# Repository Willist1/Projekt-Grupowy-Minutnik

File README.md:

## Projekt Grupowy Minutnika dla prelegentów

Zadania stawiane porjektowi według strony projektów grupowych:

https://projektgrupowy.eti.pg.gda.pl/editions/12/projects/3469

 5@KSME'2019 Minutnik do odmierzania czasu prezentacji 1-99 minut

edycja: 2019

klient: dr hab. inż. Marek Wójcikowski prof. nadzw. PG (opiekun PG)

opiekun: dr hab. inż. Marek Wójcikowski prof. nadzw. PG (KSME)

kierownik: -

W ramach projektu powinien powstać projekt oraz prototyp
sprzętowego minutnika do odmierzania czasu trwania prezentacji. Wymagane cechy
urządzenia:

- odmierzanie czasu: 1-99 minut z rozdzielczością 1 sekundy;

- zasilanie bateryjne oraz 5V (USB), opcjonalnie akumulator z
ładowaniem w urządzeniu;

- duży i jasny wyświetlacz (wysokość cyfry >40mm);

- łatwe ustawianie czasu prezentacji;

- sygnalizacja dźwiękowa:

    - ostrzeżenie przed końcem prezentacji (czas wyprzedzenia
ustawiany przez użytkownika);

    - zakończenia prezentacji;

    - możliwość wyłączenia sygnalizacji ostrzeżenia raz
zakończenia;

- pamięć ustawień po wyłączeniu zasilania;

- kompaktowe rozmiary;

- atrakcyjny wygląd.

 Zakres pracy:

- zapoznanie się z istniejącymi rozwiązaniami i dostępnymi
wyświetlaczami;

- do realizacji minutnika można wykorzystać gotowy moduł
mikrokontrolera;

- zapoznanie się z istniejącymi mikrokontrolerami;

- opracowanie interfejsu użytkownika;

- napisanie oprogramowania mikrokontrolera;

- wykonanie i uruchomienie prototypu urządzenia;

- zaprojektowanie i wykonanie obudowy (np. w technologii druku
3D);

- napisanie dokumentacji.

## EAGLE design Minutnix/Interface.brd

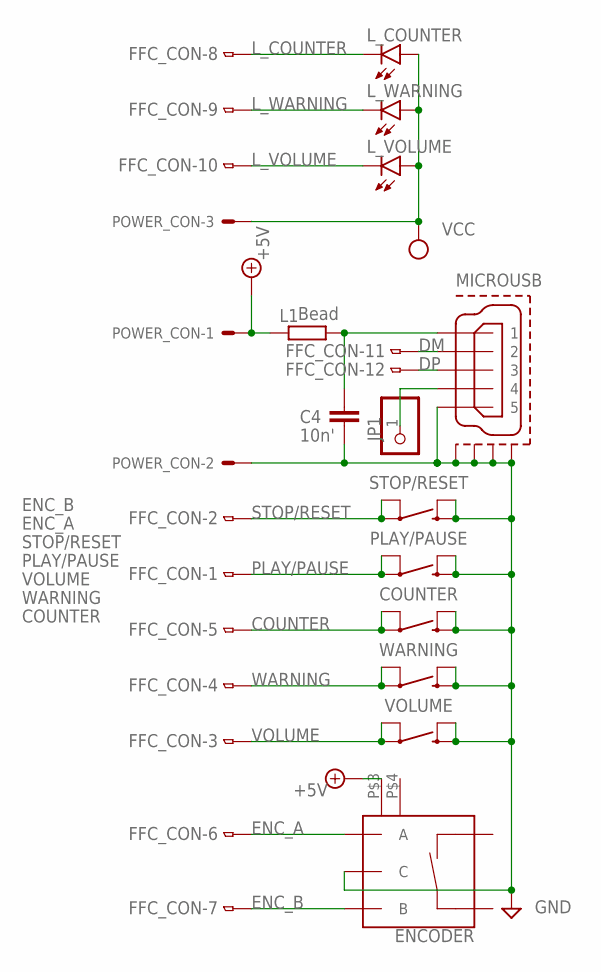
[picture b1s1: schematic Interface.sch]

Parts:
C4: 10n'; C0402
COUNTER: MOMENTARY-SWITCH-SPST-PTH-12MM; TACTILE_SWITCH_PTH_12MM
ENCODER: ENCODER-SWITCH; ROTARY_ENC_PLAIN
FFC_CON: FH12-12S-0.5S_THINNER; FH12-12S-0.5SH_THINER
JP1: PINHD-1X1; 1X01
L1: Bead; R0603
L_COUNTER: LEDCHIPLED_0805; CHIPLED_0805
L_VOLUME: LEDCHIPLED_0805; CHIPLED_0805
L_WARNING: LEDCHIPLED_0805; CHIPLED_0805
MICROUSB: MICRO-USB-RECEPTACLE; 47589-0002
PLAY/PAUSE: MOMENTARY-SWITCH-SPST-PTH-12MM; TACTILE_SWITCH_PTH_12MM
POWER_CON: JST-XH-03-PIN-LONG-PAD; JST-XH-03-PACKAGE-LONG-PAD
STOP/RESET: MOMENTARY-SWITCH-SPST-PTH-12MM; TACTILE_SWITCH_PTH_12MM
VOLUME: MOMENTARY-SWITCH-SPST-PTH-12MM; TACTILE_SWITCH_PTH_12MM
WARNING: MOMENTARY-SWITCH-SPST-PTH-12MM; TACTILE_SWITCH_PTH_12MM

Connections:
+5V: ENCODER.P$3 (GND1), L1.1, POWER_CON.1
COUNTER: COUNTER.1, COUNTER.2 (3), FFC_CON.5
DM: FFC_CON.11, MICROUSB.2
DP: FFC_CON.12, MICROUSB.3
ENC_A: ENCODER.A, FFC_CON.6
ENC_B: ENCODER.B, FFC_CON.7
GND: C4.2, COUNTER.3 (2), COUNTER.4, ENCODER.C, MICROUSB.5, MICROUSB.CASING1 (GND1), MICROUSB.CASING2 (GND2), MICROUSB.CASING3 (GND3), MICROUSB.CASING4 (GND4), PLAY/PAUSE.3 (2), PLAY/PAUSE.4, POWER_CON.2, STOP/RESET.3 (2), STOP/RESET.4, VOLUME.3 (2), VOLUME.4, WARNING.3 (2), WARNING.4
L_COUNTER: FFC_CON.8, L_COUNTER.C
L_VOLUME: FFC_CON.10, L_VOLUME.C
L_WARNING: FFC_CON.9, L_WARNING.C
unnamed: JP1.1, MICROUSB.4
unnamed: C4.1, L1.2, MICROUSB.1
PLAY/PAUSE: FFC_CON.1, PLAY/PAUSE.1, PLAY/PAUSE.2 (3)
STOP/RESET: FFC_CON.2, STOP/RESET.1, STOP/RESET.2 (3)
VCC: L_COUNTER.A, L_VOLUME.A, L_WARNING.A, POWER_CON.3
VOLUME: FFC_CON.3, VOLUME.1, VOLUME.2 (3)
WARNING: FFC_CON.4, WARNING.1, WARNING.2 (3)

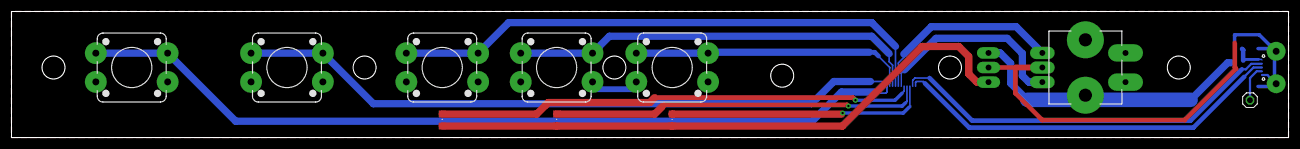
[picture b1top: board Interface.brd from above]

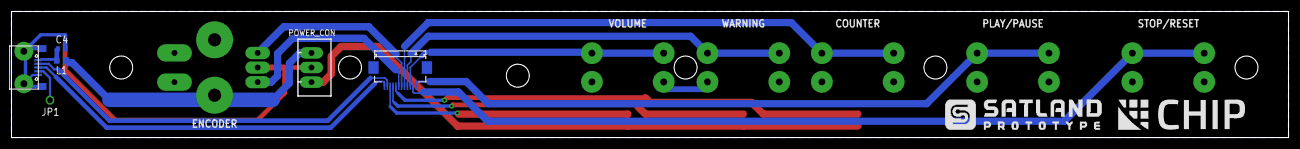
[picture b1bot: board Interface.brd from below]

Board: 2 copper layers, 222.3 x 21.9 mm, 15 parts (5 on the bottom side), 17 nets.

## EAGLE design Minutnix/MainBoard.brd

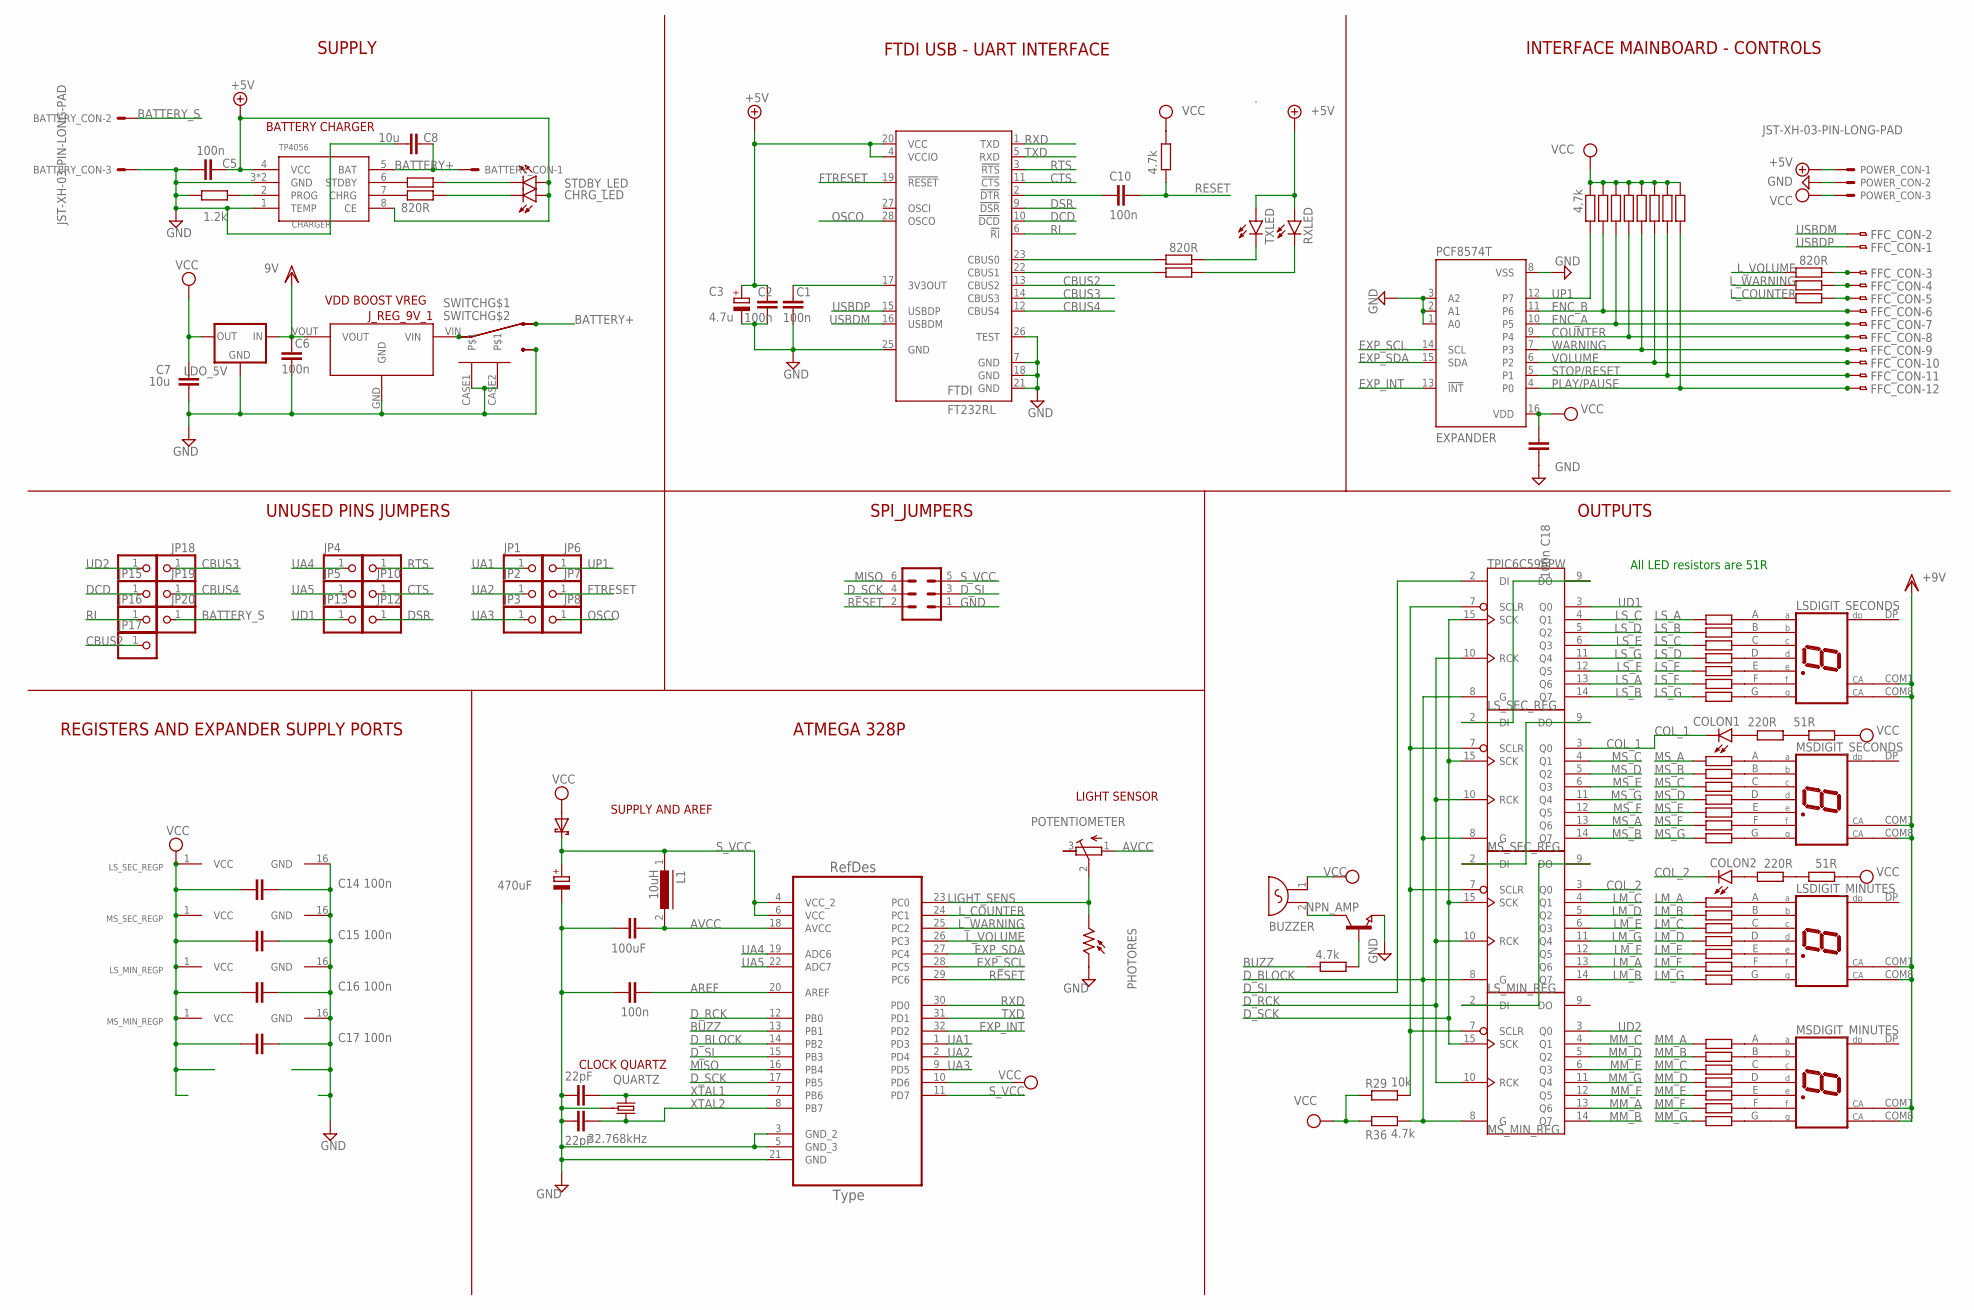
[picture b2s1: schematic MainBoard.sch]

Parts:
ATMEGA328P: ATMEGA328P-AU; QFP80P900X900X120-32N
BATTERY_CON: JST-XH-03-PIN-LONG-PAD; JST-XH-03-PACKAGE-LONG-PAD
BUZZER: F/HGP
C1, C2, C4, C5, C6, C10, C14, C15, C16, C17, C18: 100n; C0603
C3: 4.7u; SMC_B
C7, C8: 10u; C1206
C29, C30: 22pF; C0603
C31: 470uF; 153CLV-0810
C32: 100uF; C1210
CHARGER: TP4056; SOP-8
CHRG_LED: LEDCHIPLED_0603; CHIPLED_0603
COLON1, COLON2: LED5MM
EXPANDER: PCF8574T; SO16W
FFC_CON: FH12-12S-0.5S_THINNER; FH12-12S-0.5SH_THINER
FTDI: FT232RL; SSOP28
JP1, JP2, JP3, JP4, JP5, JP6, JP7, JP8, JP9, JP10, JP12, JP13, JP14, JP15, JP16, JP17, JP18, JP19, JP20: PINHD-1X1; 1X01
J_REG_9V_1: 9V_VOLTAGE_REGULATOR
L1: 10uH; DR73
LDO_5V: LM1117; SOT223
LSDIGIT_MINUTES: LED-7-SEGM-56MM; MYTHT
LSDIGIT_SECONDS: LED-7-SEGM-56MM; MYTHT
LS_MIN_REG: TPIC6C596PW; SO16
LS_SEC_REG: TPIC6C596PW; SO16
MSDIGIT_MINUTES: LED-7-SEGM-56MM; MYTHT
MSDIGIT_SECONDS: LED-7-SEGM-56MM; MYTHT
MS_MIN_REG: TPIC6C596PW; SO16
MS_SEC_REG: TPIC6C596PW; SO16
NPN_AMP: NPN-TRANSISTOR_SOT23; SOT23
PHOTORES: VT90N1; VT900
POTENTIOMETER: R-TRIMM3296Y; RTRIM3296Y
POWER_CON: JST-XH-03-PIN-LONG-PAD; JST-XH-03-PACKAGE-LONG-PAD
QUARTZ: 32.768kHz; CRYSTAL-SMD-2X6-CYL
R1, R2, R3, R4, R5, R6, R7, R8, R9, R10, R11, R12, R13, R14, R15, R16, R17, R18, R19, R20, R21, R22, R23, R24, R25, R26, R27, R28: 50; R0603
R29: 10k; R0603
R30, R31, R33, R36, R42, R43, R44, R45, R46, R56, R61: 4.7k; R0603
R32, R35: 51R; R0603
R34, R50: 220R; R0603
R39, R40, R47, R52, R64, R65, R66: 820R; R0603
R48: 1.2k; R0603
RXLED: LEDCHIPLED_0603; CHIPLED_0603
SHOTTKY: S2A; DO214AA
SPI_JUMPERS: MA03-2
STDBY_LED: LEDCHIPLED_0603; CHIPLED_0603
SWITCH: X2; MINI
TXLED: LEDCHIPLED_0603; CHIPLED_0603

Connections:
+5V: C2.2, C3.+, C5.1, CHARGER.4 (VCC), CHARGER.8 (CE), CHRG_LED.A, FTDI.4 (VCCIO), FTDI.20 (VCC), POWER_CON.1, RXLED.A, STDBY_LED.A, TXLED.A
AREF: ATMEGA328P.20 (AREF), C4.1
AVCC: ATMEGA328P.18 (AVCC), C32.1, L1.2, POTENTIOMETER.1 (A)
BATTERY+: BATTERY_CON.1, C8.2, CHARGER.5 (BAT), SWITCH.1, SWITCH.4
BATTERY_S: BATTERY_CON.2, JP20.1
BUZZ: ATMEGA328P.13 (PB1), R30.2
CBUS2: FTDI.13 (CBUS2), JP17.1
CBUS3: FTDI.14 (CBUS3), JP18.1
CBUS4: FTDI.12 (CBUS4), JP19.1
COL_1: COLON1.K (C), MS_SEC_REG.3 (Q0)
COL_2: COLON2.K (C), LS_MIN_REG.3 (Q0)
COUNTER: EXPANDER.9 (P4), FFC_CON.8, R42.2
CTS: FTDI.11 (!CTS), JP10.1
DCD: FTDI.10 (!DCD), JP15.1
DSR: FTDI.9 (!DSR), JP12.1
DTR: C10.2, FTDI.2 (!DTR)
D_BLOCK: ATMEGA328P.14 (PB2), LS_MIN_REG.8 (G), LS_SEC_REG.8 (G), MS_MIN_REG.8 (G), MS_SEC_REG.8 (G), R36.1
D_RCK: ATMEGA328P.12 (PB0), LS_MIN_REG.10 (RCK), LS_SEC_REG.10 (RCK), MS_MIN_REG.10 (RCK), MS_SEC_REG.10 (RCK)
D_SCK: ATMEGA328P.17 (PB5), LS_MIN_REG.15 (SCK), LS_SEC_REG.15 (SCK), MS_MIN_REG.15 (SCK), MS_SEC_REG.15 (SCK), SPI_JUMPERS.4
D_SI: ATMEGA328P.15 (PB3), LS_SEC_REG.2 (DI), SPI_JUMPERS.3
ENC_A: EXPANDER.10 (P5), FFC_CON.7, R33.2
ENC_B: EXPANDER.11 (P6), FFC_CON.6, R31.2
EXP_INT: ATMEGA328P.32 (PD2), EXPANDER.13 (!INT)
EXP_SCL: ATMEGA328P.28 (PC5), EXPANDER.14 (SCL)
EXP_SDA: ATMEGA328P.27 (PC4), EXPANDER.15 (SDA)
FTRESET: FTDI.19 (!RESET), JP7.1
GND: ATMEGA328P.3 (GND_2), ATMEGA328P.5 (GND_3), ATMEGA328P.21 (GND), BATTERY_CON.3, C1.1, C2.1, C3.-, C4.2, C5.2, C6.1, C7.2, C8.1, C14.1, C15.1, C16.1, C17.1, C18.1, C29.1, C30.1, C31.-, C32.2, CHARGER.1 (TEMP), CHARGER.3 (GND), CHARGER.ETP (GND), EXPANDER.1 (A0), EXPANDER.2 (A1), EXPANDER.3 (A2), EXPANDER.8 (VSS), FTDI.7 (GND), FTDI.18 (GND), FTDI.21 (GND), FTDI.25 (GND), FTDI.26 (TEST), J_REG_9V_1.GND, LDO_5V.1 (GND), LS_MIN_REG.16 (GND), LS_SEC_REG.16 (GND), MS_MIN_REG.16 (GND), MS_SEC_REG.16 (GND), NPN_AMP.2 (E), PHOTORES.1, POWER_CON.2, QUARTZ.SHEILD (GND), R48.2, SPI_JUMPERS.1, SWITCH.3, SWITCH.6, SWITCH.CASE1, SWITCH.CASE2
LIGHT_SENS: ATMEGA328P.23 (PC0), PHOTORES.2, POTENTIOMETER.2 (S)
LM_A: LS_MIN_REG.13 (Q6), R7.2
LM_B: LS_MIN_REG.14 (Q7), R6.2
LM_C: LS_MIN_REG.4 (Q1), R5.2
LM_D: LS_MIN_REG.5 (Q2), R4.2
LM_E: LS_MIN_REG.6 (Q3), R3.2
LM_F: LS_MIN_REG.12 (Q5), R2.2
LM_G: LS_MIN_REG.11 (Q4), R1.2
LS_A: LS_SEC_REG.13 (Q6), R21.2
LS_B: LS_SEC_REG.14 (Q7), R20.2
LS_C: LS_SEC_REG.4 (Q1), R19.2
LS_D: LS_SEC_REG.5 (Q2), R18.2
LS_E: LS_SEC_REG.6 (Q3), R17.2
LS_F: LS_SEC_REG.12 (Q5), R16.2
LS_G: LS_SEC_REG.11 (Q4), R15.2
L_COUNTER: ATMEGA328P.24 (PC1), R52.2
L_VOLUME: ATMEGA328P.26 (PC3), R64.2
L_WARNING: ATMEGA328P.25 (PC2), R47.2
MISO: ATMEGA328P.16 (PB4), SPI_JUMPERS.6
MM_A: MS_MIN_REG.13 (Q6), R27.2
MM_B: MS_MIN_REG.14 (Q7), R26.2
MM_C: MS_MIN_REG.4 (Q1), R25.2
MM_D: MS_MIN_REG.5 (Q2), R24.2
MM_E: MS_MIN_REG.6 (Q3), R23.2
MM_F: MS_MIN_REG.12 (Q5), R22.2
MM_G: MS_MIN_REG.11 (Q4), R28.2
MS_A: MS_SEC_REG.13 (Q6), R14.2
MS_B: MS_SEC_REG.14 (Q7), R13.2
MS_C: MS_SEC_REG.4 (Q1), R12.2
MS_D: MS_SEC_REG.5 (Q2), R11.2
MS_E: MS_SEC_REG.6 (Q3), R10.2
MS_F: MS_SEC_REG.12 (Q5), R9.2
MS_G: MS_SEC_REG.11 (Q4), R8.2
unnamed: R32.2, R50.1
unnamed: MSDIGIT_MINUTES.F, R22.1
unnamed: LSDIGIT_MINUTES.G, R1.1
unnamed: MSDIGIT_MINUTES.E, R23.1
unnamed: LSDIGIT_MINUTES.F, R2.1
unnamed: LSDIGIT_MINUTES.E, R3.1
unnamed: LSDIGIT_MINUTES.D, R4.1
unnamed: LSDIGIT_MINUTES.C, R5.1
unnamed: LSDIGIT_MINUTES.B, R6.1
unnamed: FFC_CON.3, R64.1
unnamed: MSDIGIT_MINUTES.D, R24.1
unnamed: FFC_CON.4, R47.1
unnamed: MSDIGIT_MINUTES.C, R25.1
unnamed: LS_MIN_REG.7 (SCLR), LS_SEC_REG.7 (SCLR), MS_MIN_REG.7 (SCLR), MS_SEC_REG.7 (SCLR), R29.1
unnamed: LSDIGIT_MINUTES.A, R7.1
unnamed: C1.2, FTDI.17 (3V3OUT)
unnamed: COLON2.A, R34.2
unnamed: FFC_CON.5, R52.1
unnamed: MSDIGIT_MINUTES.B, R26.1
unnamed: MSDIGIT_MINUTES.A, R27.1
unnamed: MSDIGIT_SECONDS.G, R8.1
unnamed: MSDIGIT_SECONDS.F, R9.1
unnamed: MSDIGIT_SECONDS.E, R10.1
unnamed: FTDI.23 (CBUS0), R66.2
unnamed: MSDIGIT_SECONDS.D, R11.1
unnamed: MSDIGIT_SECONDS.C, R12.1
unnamed: MSDIGIT_SECONDS.B, R13.1
unnamed: MSDIGIT_SECONDS.A, R14.1
unnamed: LSDIGIT_SECONDS.G, R15.1
unnamed: LSDIGIT_SECONDS.F, R16.1
unnamed: FTDI.22 (CBUS1), R65.2
unnamed: LSDIGIT_SECONDS.E, R17.1
unnamed: LSDIGIT_SECONDS.D, R18.1
unnamed: LSDIGIT_SECONDS.C, R19.1
unnamed: LSDIGIT_SECONDS.B, R20.1
unnamed: LSDIGIT_SECONDS.A, R21.1
unnamed: R34.1, R35.2
unnamed: CHARGER.7 (CHRG), R39.2
unnamed: CHARGER.6 (STDBY), R40.2
unnamed: CHRG_LED.C, R39.1
unnamed: R40.1, STDBY_LED.C
unnamed: COLON1.A, R50.2
unnamed: MSDIGIT_MINUTES.G, R28.1
unnamed: R66.1, TXLED.C
unnamed: NPN_AMP.1 (B), R30.1
unnamed: BUZZER.2, NPN_AMP.3 (C)
unnamed: R65.1, RXLED.C
unnamed: LS_MIN_REG.2 (DI), MS_SEC_REG.9 (DO)
unnamed: LS_MIN_REG.9 (DO), MS_MIN_REG.2 (DI)
unnamed: LS_SEC_REG.9 (DO), MS_SEC_REG.2 (DI)
unnamed: J_REG_9V_1.VIN, SWITCH.2, SWITCH.5
unnamed: CHARGER.2 (PROG), R48.1
OSCO: FTDI.28 (OSCO), JP8.1
PLAY/PAUSE: EXPANDER.4 (P0), FFC_CON.12, R46.2
RESET: ATMEGA328P.29 (PC6), C10.1, R56.1, SPI_JUMPERS.2
RI: FTDI.6 (!RI), JP16.1
RTS: FTDI.3 (!RTS), JP9.1
RXD: ATMEGA328P.30 (PD0), FTDI.1 (TXD)
STOP/RESET: EXPANDER.5 (P1), FFC_CON.11, R45.2
S_VCC: ATMEGA328P.4 (VCC_2), ATMEGA328P.6 (VCC), ATMEGA328P.11 (PD7), C31.+, L1.1, SHOTTKY.C, SPI_JUMPERS.5
TXD: ATMEGA328P.31 (PD1), FTDI.5 (RXD)
UA1: ATMEGA328P.1 (PD3), JP1.1
UA2: ATMEGA328P.2 (PD4), JP2.1
UA3: ATMEGA328P.9 (PD5), JP3.1
UA4: ATMEGA328P.19 (ADC6), JP4.1
UA5: ATMEGA328P.22 (ADC7), JP5.1
UD1: JP13.1, LS_SEC_REG.3 (Q0)
UD2: JP14.1, MS_MIN_REG.3 (Q0)
UP1: EXPANDER.12 (P7), JP6.1, R61.2
USBDM: FFC_CON.2, FTDI.16 (USBDM)
USBDP: FFC_CON.1, FTDI.15 (USBDP)
VCC: ATMEGA328P.10 (PD6), BUZZER.1, C7.1, C14.2, C15.2, C16.2, C17.2, C18.2, EXPANDER.16 (VDD), LDO_5V.2 (OUT), LDO_5V.4 (OUT), LS_MIN_REG.1 (VCC), LS_SEC_REG.1 (VCC), MS_MIN_REG.1 (VCC), MS_SEC_REG.1 (VCC), POWER_CON.3, R29.2, R31.1, R32.1, R33.1, R35.1, R36.2, R42.1, R43.1, R44.1, R45.1, R46.1, R56.2, R61.1, SHOTTKY.A
VDD: C6.2, J_REG_9V_1.VOUT, LDO_5V.3 (IN), LSDIGIT_MINUTES.COM1 (CA1), LSDIGIT_MINUTES.COM8 (CA8), LSDIGIT_SECONDS.COM1 (CA1), LSDIGIT_SECONDS.COM8 (CA8), MSDIGIT_MINUTES.COM1 (CA1), MSDIGIT_MINUTES.COM8 (CA8), MSDIGIT_SECONDS.COM1 (CA1), MSDIGIT_SECONDS.COM8 (CA8)
VOLUME: EXPANDER.6 (P2), FFC_CON.10, R44.2
WARNING: EXPANDER.7 (P3), FFC_CON.9, R43.2
XTAL1: ATMEGA328P.7 (PB6), C29.2, QUARTZ.X2 (2)
XTAL2: ATMEGA328P.8 (PB7), C30.2, QUARTZ.X1 (1)

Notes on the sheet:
All LED resistors are 51R
LIGHT SENSOR
INTERFACE MAINBOARD - CONTROLS
FTDI USB - UART INTERFACE
UNUSED PINS JUMPERS
SUPPLY AND AREF
CLOCK QUARTZ
VDD BOOST VREG
REGISTERS AND EXPANDER SUPPLY PORTS
BATTERY CHARGER
SUPPLY
ATMEGA 328P
OUTPUTS

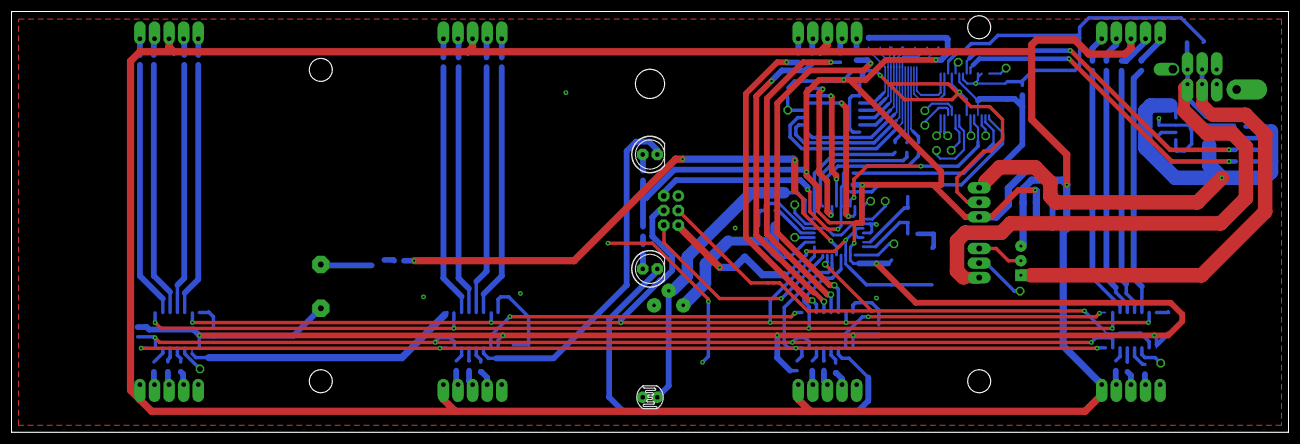
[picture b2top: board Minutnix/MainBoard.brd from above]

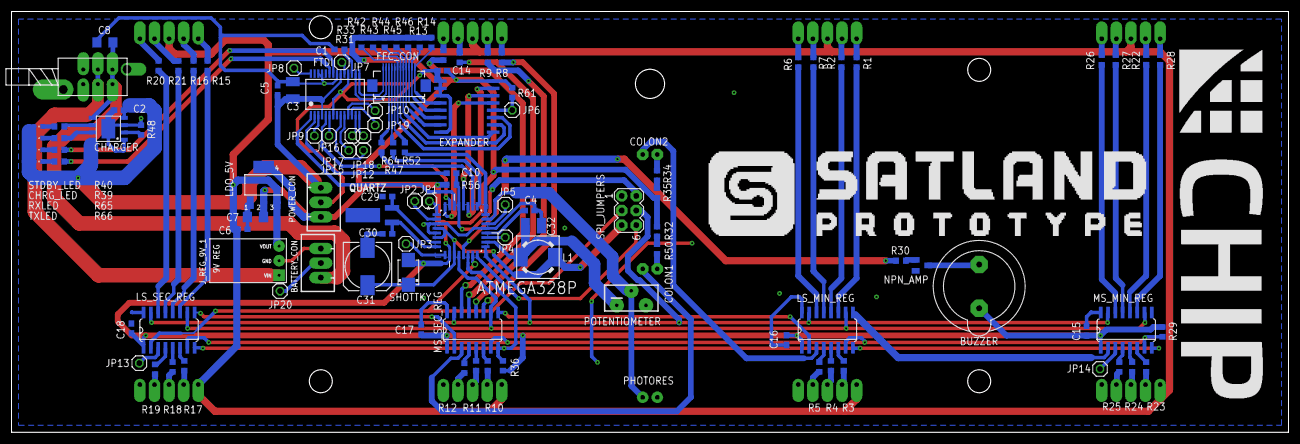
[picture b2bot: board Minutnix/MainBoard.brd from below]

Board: 2 copper layers, 222.3 x 73.3 mm, 121 parts (114 on the bottom side), 137 nets.

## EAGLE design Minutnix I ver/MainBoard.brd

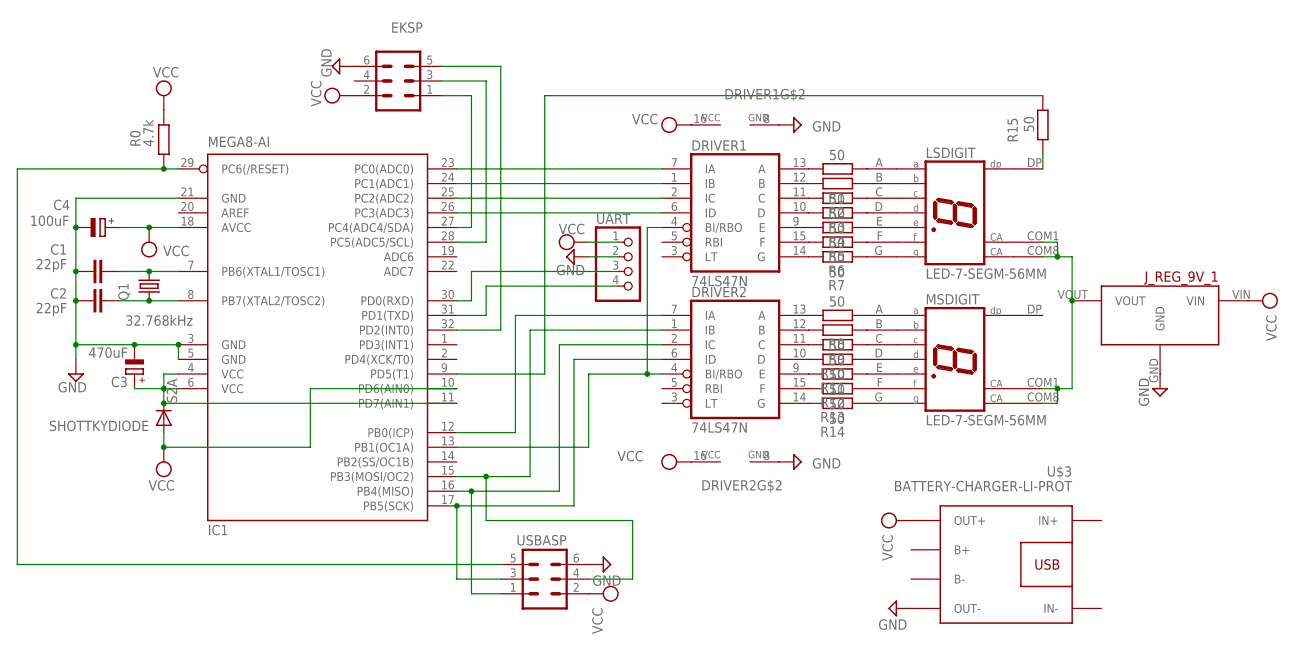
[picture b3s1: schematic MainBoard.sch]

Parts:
C1, C2: 22pF; C2.5-2
C3: 470uF; 140CLH-1010
C4: 100uF; 140CLH-1010
DRIVER1, DRIVER2: 74LS47N; DIL16
EKSP: ML6
IC1: MEGA8-AI; TQFP32-08
J_REG_9V_1: 9V_VOLTAGE_REGULATOR
LSDIGIT: LED-7-SEGM-56MM; MYTHT
MSDIGIT: LED-7-SEGM-56MM; MYTHT
Q1: 32.768kHz; TC26V
R0: 4.7k; R01005
R1, R2, R3, R4, R5, R6, R7, R8, R9, R10, R11, R12, R13, R14, R15: 50; R01005
SHOTTKYDIODE: S2A; DO214AA
U$3: BATTERY-CHARGER-LI-PROT
UART: PINHD-1X4; 1X04
USBASP: ML6

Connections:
GND: C1.1, C2.1, C3.-, C4.-, DRIVER1.8 (GND), DRIVER2.8 (GND), EKSP.6, IC1.3 (GND), IC1.5 (GND), IC1.21 (GND), J_REG_9V_1.GND, U$3.OUT-, UART.2, USBASP.6
unnamed: C1.2, IC1.7 (PB6(XTAL1/TOSC1)), Q1.2
unnamed: C2.2, IC1.8 (PB7(XTAL2/TOSC2)), Q1.1
unnamed: DRIVER2.7 (IA), IC1.12 (PB0(ICP))
unnamed: DRIVER1.4 (BI/RBO), DRIVER2.4 (BI/RBO), IC1.13 (PB1(OC1A))
unnamed: DRIVER1.13 (A), R1.2
unnamed: DRIVER1.12 (B), R2.2
unnamed: DRIVER1.11 (C), R3.2
unnamed: DRIVER1.10 (D), R4.2
unnamed: DRIVER1.9 (E), R5.2
unnamed: DRIVER1.15 (F), R6.2
unnamed: DRIVER1.14 (G), R7.2
unnamed: EKSP.1, IC1.27 (PC4(ADC4/SDA))
unnamed: LSDIGIT.A, R1.1
unnamed: EKSP.5, IC1.32 (PD2(INT0))
unnamed: LSDIGIT.B, R2.1
unnamed: LSDIGIT.C, R3.1
unnamed: LSDIGIT.D, R4.1
unnamed: LSDIGIT.E, R5.1
unnamed: LSDIGIT.F, R6.1
unnamed: EKSP.3, IC1.28 (PC5(ADC5/SCL))
unnamed: DRIVER2.6 (ID), IC1.17 (PB5(SCK)), USBASP.3
unnamed: IC1.29 (PC6(/RESET)), R0.1, USBASP.5
unnamed: DRIVER2.1 (IB), IC1.15 (PB3(MOSI/OC2)), USBASP.4
unnamed: DRIVER2.2 (IC), IC1.16 (PB4(MISO)), USBASP.1
unnamed: LSDIGIT.G, R7.1
unnamed: DRIVER1.7 (IA), IC1.23 (PC0(ADC0))
unnamed: DRIVER1.1 (IB), IC1.24 (PC1(ADC1))
unnamed: DRIVER1.2 (IC), IC1.25 (PC2(ADC2))
unnamed: DRIVER1.6 (ID), IC1.26 (PC3(ADC3))
unnamed: IC1.31 (PD1(TXD)), UART.4
unnamed: IC1.30 (PD0(RXD)), UART.3
unnamed: LSDIGIT.DP, R15.1
unnamed: IC1.9 (PD5(T1)), R15.2
unnamed: MSDIGIT.A, R8.1
unnamed: C3.+, IC1.4 (VCC), IC1.6 (VCC), IC1.11 (PD7(AIN1)), SHOTTKYDIODE.C
unnamed: J_REG_9V_1.VOUT, LSDIGIT.COM1 (CA1), LSDIGIT.COM8 (CA8), MSDIGIT.COM1 (CA1), MSDIGIT.COM8 (CA8)
unnamed: MSDIGIT.B, R9.1
unnamed: MSDIGIT.C, R10.1
unnamed: MSDIGIT.D, R11.1
unnamed: MSDIGIT.E, R12.1
unnamed: MSDIGIT.F, R13.1
unnamed: MSDIGIT.G, R14.1
unnamed: DRIVER2.14 (G), R14.2
unnamed: DRIVER2.15 (F), R13.2
unnamed: DRIVER2.9 (E), R12.2
unnamed: DRIVER2.10 (D), R11.2
unnamed: DRIVER2.11 (C), R10.2
unnamed: DRIVER2.12 (B), R9.2
unnamed: DRIVER2.13 (A), R8.2
VCC: C4.+, DRIVER1.16 (VCC), DRIVER2.16 (VCC), EKSP.2, IC1.10 (PD6(AIN0)), IC1.18 (AVCC), J_REG_9V_1.VIN, R0.2, SHOTTKYDIODE.A, U$3.OUT+, UART.1, USBASP.2

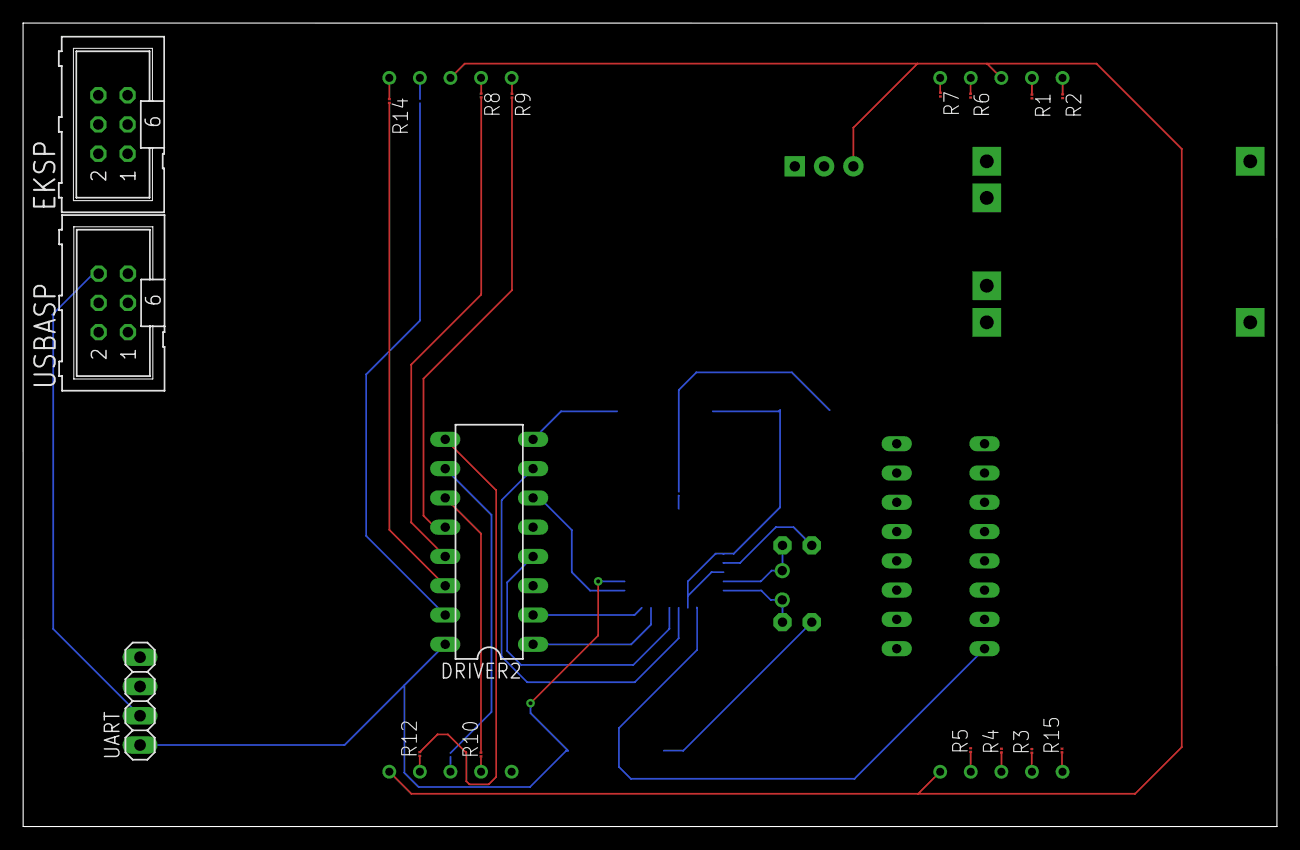
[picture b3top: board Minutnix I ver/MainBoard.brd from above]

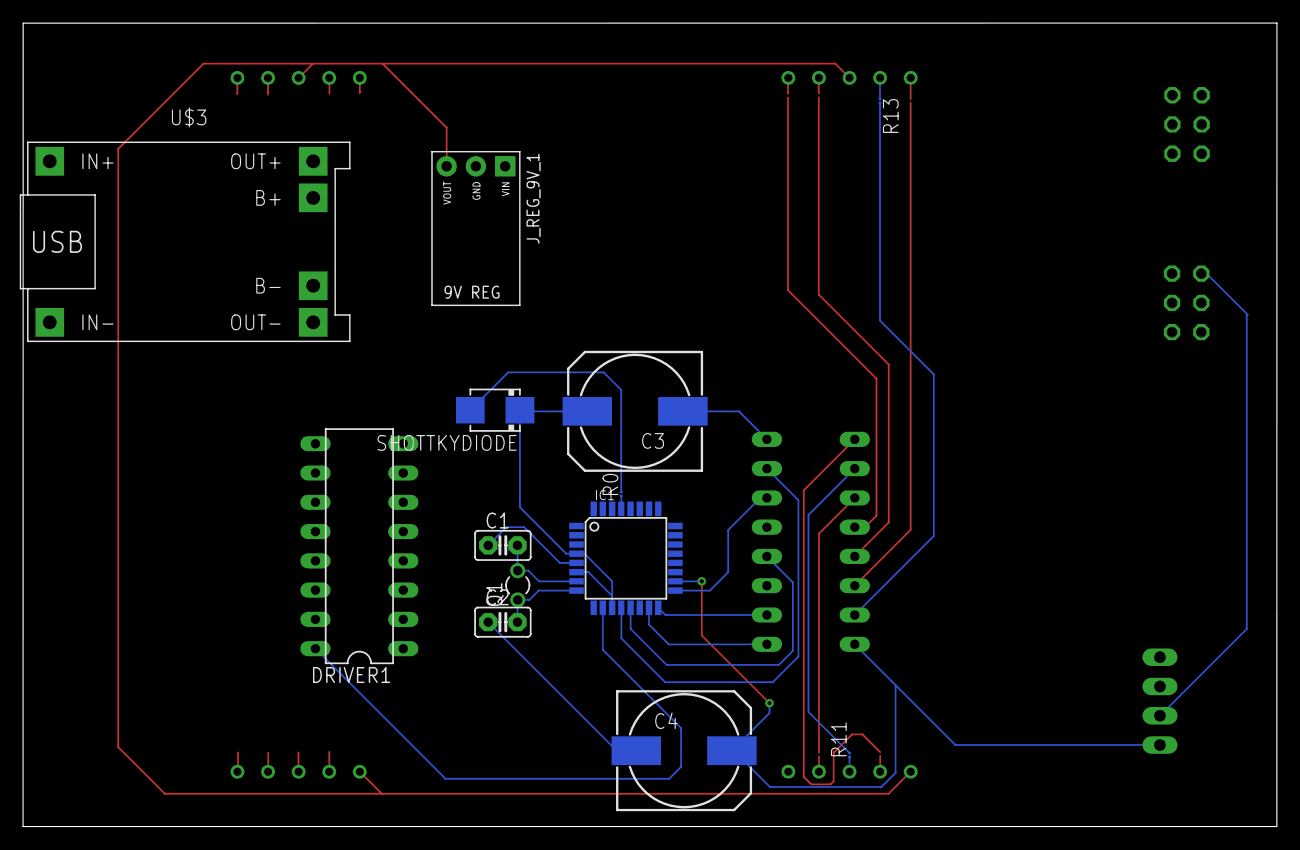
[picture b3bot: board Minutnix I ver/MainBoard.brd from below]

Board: 2 copper layers, 108.8 x 69.7 mm, 32 parts (13 on the bottom side), 51 nets.

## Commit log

2019-02-28 New project
2019-03-10 Schematic first draft
2019-03-10 Removed empty old AS7 project
2019-03-10 Added new AS7 project
    Implemented functionalities:
    - 7-seg display multiplexing (with dimming)
    - communication with PCF8574 expander
    - external interrupt from expander detection
    - added source code for usart debug via std stream
2019-03-13 Added functions for reading and interpreting encoder signals
    Additionally fixed digit mapping
2019-03-14 Implemented SysTick and PWM for buzzer volume control
2019-03-14 Prepared power failure handling code
2019-03-19 Implemented user interface
2019-03-21 Main board V1
2019-03-21 First draft of board (correct displays)
    Resistors and capacitors not chosen yet,
    Goldpin on battery removed - will be directly on board
2019-03-23 Prepared pwr failure detection
2019-03-23 Adjusted pinout in code to electronic schematic
2019-03-23 Implemented nvdata saving and restoral
2019-03-24 Implemented watchdog and sleep mode
2019-03-24 Small corrections
    Disabling watchdog in sleep mode
2019-03-24 Corretcion
    Corrected max no activity time
2019-03-24 Fixed fwr fail procedure and brightness setting
2019-03-24 Saving config when turned off in sleep mode
    Added dot blinking in running state
2019-03-24 Fixed dot jitter in running state, remove dot blining in setting state
2019-03-27 Add First Draft of 3D model
    For documentation of first prototype.
2019-03-27 Add first draft image
2019-03-29 Wersja 1
    Do kubełka 1
2019-04-03 Archivisation and actualisation
    Archivisation of 1 version of boards
    New version of boards
2019-04-11 Adaptation to PCF8574AP
2019-04-20 4-digit display with shift regs
2019-04-28 New menu engine, implemented light sensor, added setting leds, piezo beeper control
2019-04-28 Fixed issue with brightness control after startup
2019-04-28 Small clean-up
2019-04-28 Minor board changes
2019-04-28 Pullup for displays
    +removed trash
2019-04-28 Fixed wrong encoder reading processing after pressing stop
2019-04-28 Small corrections in comments and enums
2019-04-28 Changed sleep condition
2019-05-03 Power boards incorporated
    Redrawn power supply circuits so we use one PCB
2019-05-03 Newest Corrected schematic
    Splited into diffrent sheets. Improoved readability.
2019-05-16 Swapped pins 13 and 14
2019-05-16 Vreg done, formatting
    TODO:
    solve offgrid
    check charger circuit if proper
2019-05-19 Buzzer migration, RCK pin change, : behave
    RCK -> PB0
    BUZZER -> OCR1A
    : blink on pause, constant on running
2019-05-23 Prevented pause on finish, added external crystal clock
2019-05-26 After meeting corrections
    New pause mode
    Brightness map inverted
    Max warning time restricted
    Buzzer fixed
    UART fixed (F_CPU flag changed)
    Pwr Fail procedure delay corrected
2019-05-26 Implemented EEPROM wear leveling
    Extended durability 10x
2019-05-27 Uploading bootloader
2019-05-27 Added useful links in readme file
2019-05-31 Updated pinout
2019-10-03 Corrected AS7 external tools description
2019-10-06 Update MainBoard.sch
    Corrected some values, added descriptions and some typos.
2019-10-12 Minor changes in pin config
2019-10-12 After review corrections
    W programie LEDy od dwukropka sa kropkami dwoch srodkowych wyswietlaczy (wariant w ktorym segmenty wyswietlacza sa obslugiwane przez dwa osobbe rejestry przesuwny jest niekorzystny programowo)
    Light sensor powinien byc podlaczony do PC0 [L1] (olewamy ADC6)
    Czy na pewno podlaczenie TX ATmegi do TX FTDI ma sens? Nie powinno byc crossowania? (oznaczenie TX dotyczy ATmegi)
    Nowe podlaczenie pinow PCF na schematach (nie uzyc pinu P7)
    Usunac przyciski z podswietleniem (przyciskow jest 5), 3 LEDy sygnalizujace wybrana opcje ustawien wlaczane stanem niskim na pinie ATmegi (P1 - P3)
    Przycisk zwierajacy PD7 do masy na schemacie (dodaj do BOMu)
2019-10-27 Major board changes
    Remake of interface upper board + layout
    Majior corrections in mainboard - correct models, cables, connectors, ft232 and more. Also more libraries.
2019-10-30 Bootloader problem fix
    Changed initialization order to fix bootloader problem
2019-11-02 new lib + board progress
2019-11-02 Resistor values updated
2019-11-03 Supply replacements + corrections
    Vreg replaced by pololu board
    Added LDO for VCC supply and moved power on switch
    Protection included into battery cicruit
    Corrected supply of ft232 diodes
    Changed supply of photoresistor to avcc
2019-11-03 7segm lib + board
    Corrections on consistency and erc errors
    readded 7 segm. custom lib
    Partial components placement and routing tries
2019-11-07 libs actualisation + drc rules for expander
2019-11-07 Consolidation of schematic + lib restore
2019-11-09 Probably final routing of Expander board
    DRC 8mils clean
    libs actualisation
2019-11-09 Drc corrections
    Expander board finished:
    DRC 10mils chcecked except gaps between close pads in connector and usb
    in connector and usb drc 8mils passed
2019-11-12 lib update + board ongoing
2019-11-12 PCB with original pinout
    Register inputs unconnected but drawn close
    Not every path has optimal width
2019-11-14 Final packages
    +most paths wider (24 mils)
2019-11-14 Mixing led signals
2019-11-14 rotation of tape ports
    also some nets wider
2019-11-15 Almost complete
    Added 3d extraction
    wider better paths
    corrected Temperature field of TP to be GND
2019-11-15 Corrected programmer pins
    + added full inventor 3d model with most important dimensions
2019-11-17 Pools of gnd
    + change of lib gnd of mechanical hold
    + logos
2019-11-17 Revert "Pools of gnd"
    This reverts commit 4498ba5dce1e14fe788b06c680ced1a0feefa50f.
2019-11-17 Revert "Revert "Pools of gnd""
    This reverts commit 2f73202806bed85f49afe26d98c16d19bdefccd4.
2019-11-17 Add Logos
    add pads for tape connector
2019-11-17 Revert pools
    +Corrected isostat
2019-11-17 Mainboard Top gnd plane
2019-11-17 Main board gnd bottom pool
2019-11-17 expander pools
2019-11-18 Logos incorpoarted
    +gerbers generated
2019-11-21 Many final changes
2019-12-13 Target board programming preparation
2019-12-15 Adjusted code for PCB prototype
2020-01-10 Final actualisation
    Libs update
    Change name from Ekspander to Interface
2020-01-10 Final FW adjustments
2020-02-08 Added 20s alarm timeout & light sensor filtration

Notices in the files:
parts and their libraries:
diy-modules: Released under the Creative Commons Attribution 4.0 International License: http://creativecommons.org/licenses/by/4.0
SparkFun-Switches: Licensing: Creative Commons ShareAlike 4.0 International - https://creativecommons.org/licenses/by-sa/4.0
